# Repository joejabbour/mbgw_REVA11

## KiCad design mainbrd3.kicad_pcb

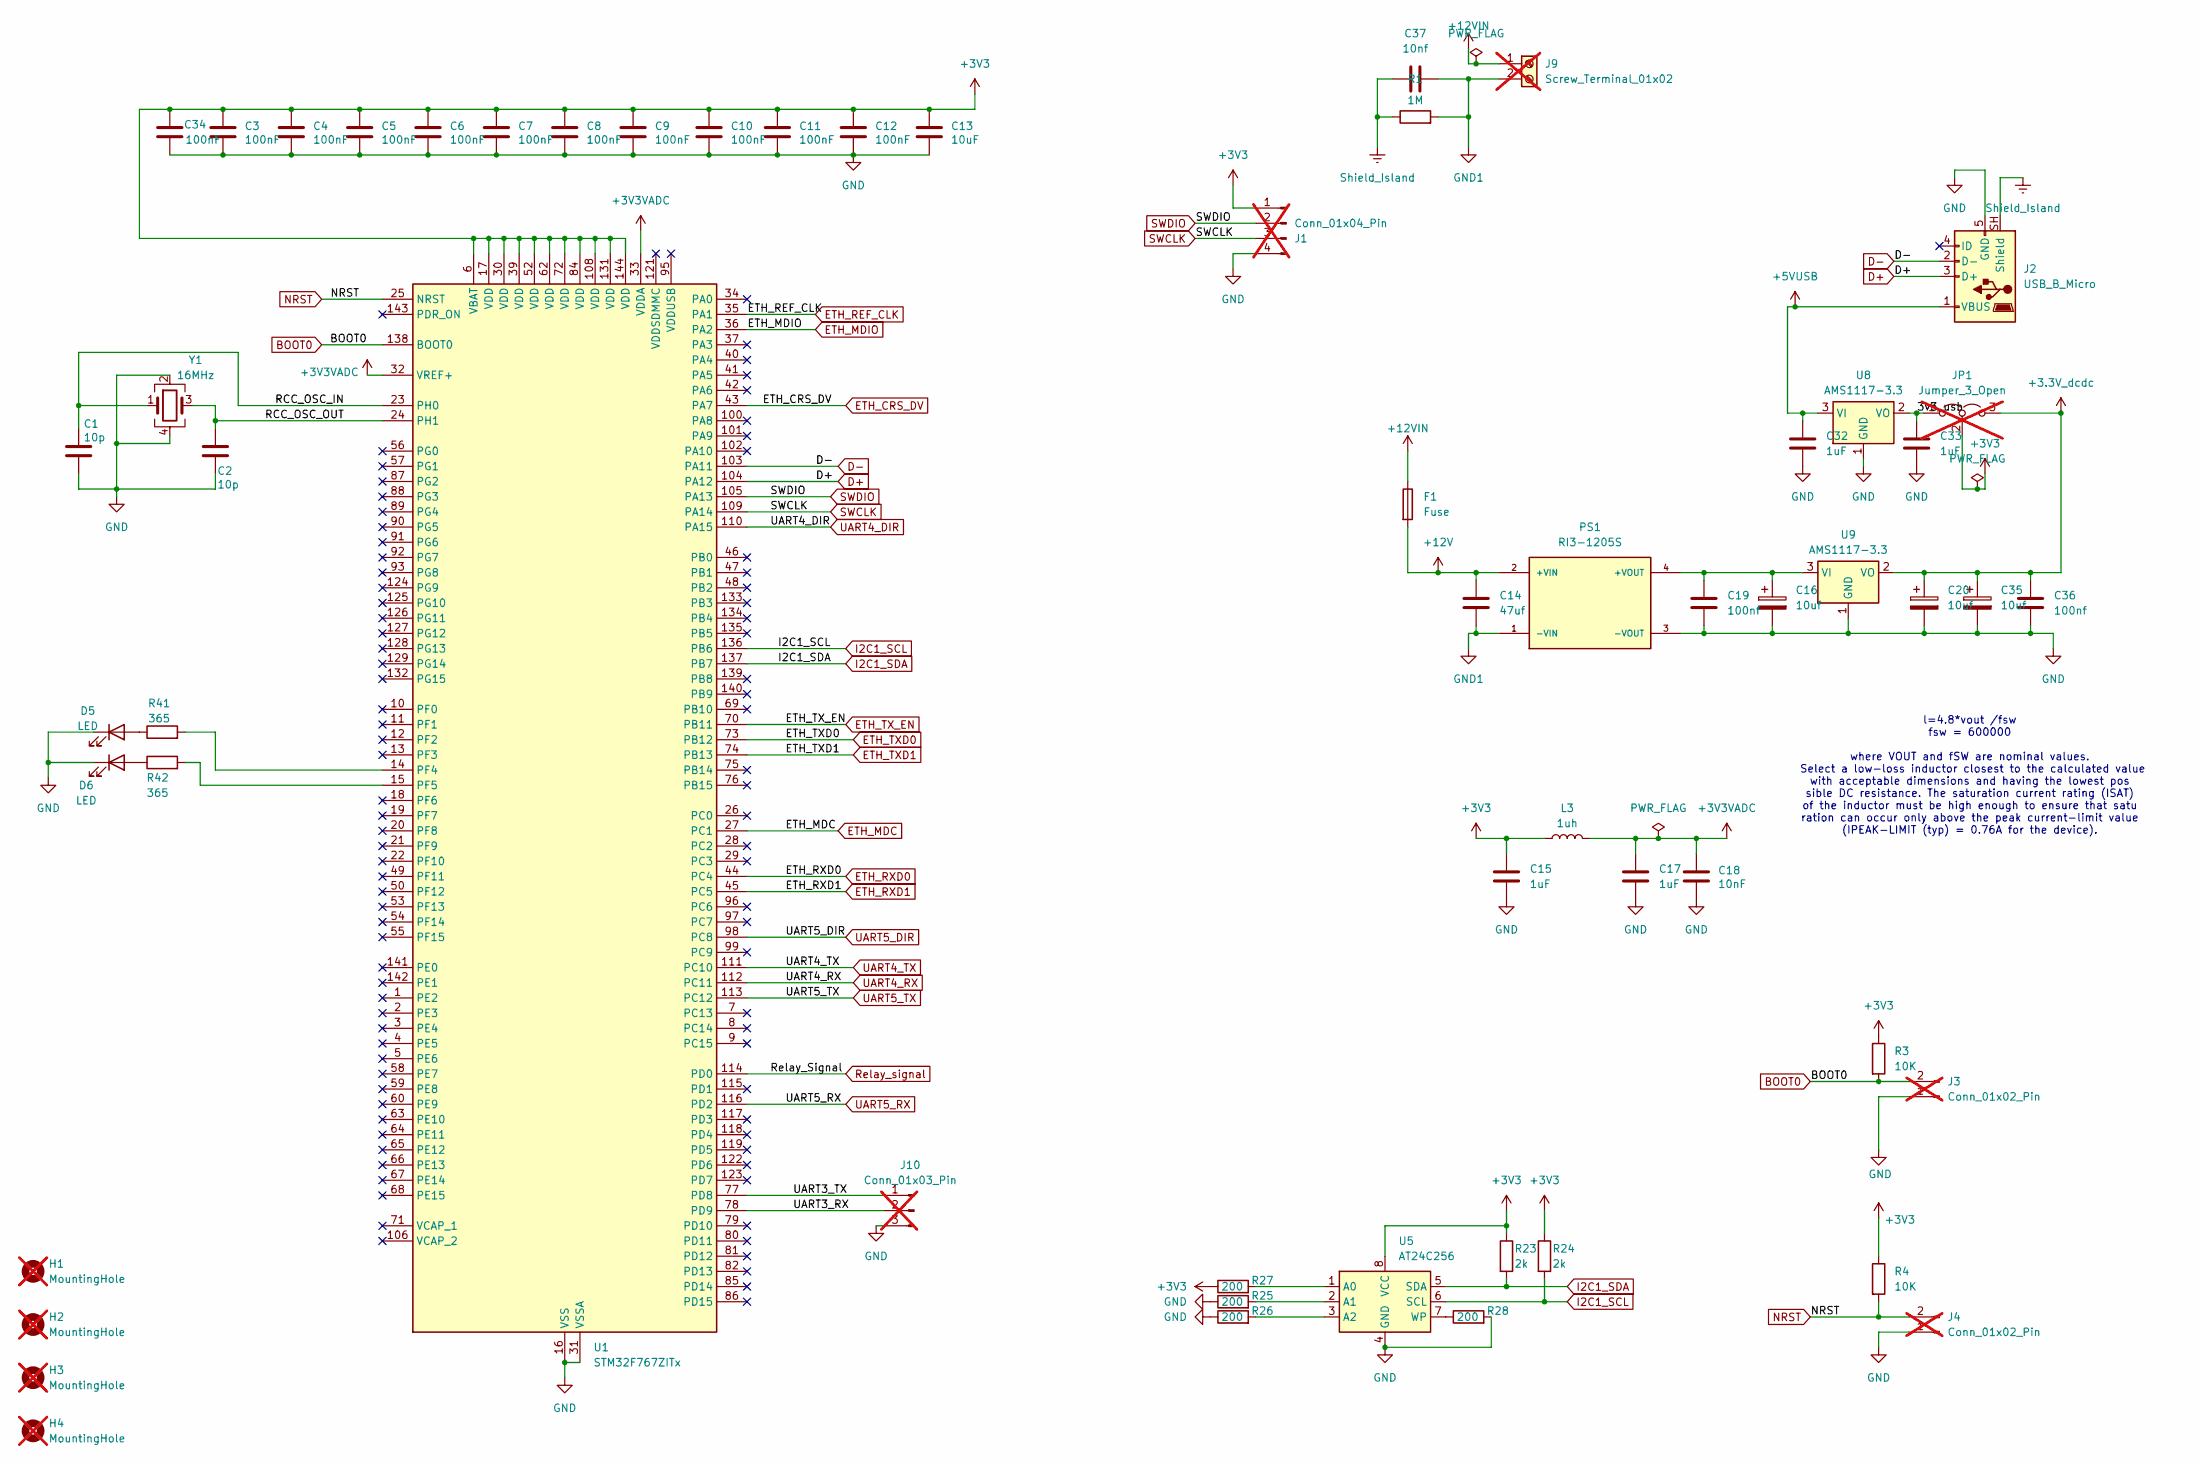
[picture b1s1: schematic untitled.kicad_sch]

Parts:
C1, C2: 10p; C_0402_1005Metric; MPN 0402CG100J500NT; JLCPCB PN C1545
C3, C4, C5, C6, C7, C8, C9, C10, C11, C12, C34: 100nF; C_0402_1005Metric; MPN 0402F104M500NT; JLCPCB PN C1581
C13: 10uF; C_0603_1608Metric; MPN CL10A106MQ8NNNC; JLCPCB PN C1691
C14: 47uf; C_1210_3225Metric; MPN GRM32ER61C476KE15L; LCSC C77101
C15, C17, C32, C33: 1uF; C_0402_1005Metric; MPN CL05A105KP5NNNC; JLCPCB PN C14445
C16, C20, C35: 10uf; CP_EIA-3216-18_Kemet-A; MPN TAJA106K016RNJ; LCSC C7171
C18: 10nF; C_0402_1005Metric; MPN 0402B103K500NT; JLCPCB PN C1524
C19, C36: 100nf; C_0402_1005Metric; MPN CC0402KRX7R7BB104; LCSC C60474
C37: 10nf; C_1812_4532Metric; MPN 1812B103K202NT; LCSC C574051
D5, D6: LED; LED_0603_1608Metric; MPN KT-0603R; JLCPCB PN C2286
F1: Fuse; Fuse_0603_1608Metric_Pad1.05x0.95mm_HandSolder; MPN 0467001.NRHF; LCSC C151139
H1, H2, H3, H4: MountingHole; MountingHole_2.2mm_M2; not fitted
J1: Conn_01x04_Pin; PinHeader_1x04_P2.54mm_Vertical; not fitted
J2: USB_B_Micro; USB_Micro-B_Wuerth_629105150521; JLCPCB PN 732-5960-2-ND(digi)
J3, J4: Conn_01x02_Pin; PinHeader_1x02_P2.54mm_Vertical; not fitted
J9: Screw_Terminal_01x02; TerminalBlock_Phoenix_MKDS-1,5-2-5.08_1x02_P5.08mm_Horizont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; not fitted
J10: Conn_01x03_Pin; PinHeader_1x03_P2.54mm_Vertical; not fitted
JP1: Jumper_3_Open; SolderJumper-3_P1.3mm_Open_Pad1.0x1.5mm; not fitted
L3: 1uh; L_0805_2012Metric; MPN MCL2012S1R0MT; JLCPCB PN C98325
PS1: RI3-1205S; CONV_RI3-1205S; PARTREV 3
R1: 1M; R_1206_3216Metric; MPN FRC1206J105 TS; LCSC C2907441
R3, R4: 10K; R_0402_1005Metric; MPN 0402WGJ0103TCE; JLCPCB PN C25531
R23, R24: 2k; R_0402_1005Metric; MPN 0402WGF2001TCE; JLCPCB PN C4109
R25, R26, R27, R28: 200; R_0402_1005Metric; MPN 0402WGF2000TCE; JLCPCB PN C25087
R41, R42: 365; R_0402_1005Metric; MPN 0402WGJ0361TCE; JLCPCB PN C25162
U1: STM32F767ZITx; LQFP-144_20x20mm_P0.5mm; MPN STM32F767ZIT6; JLCPCB PN C90235
U5: AT24C256; SOIC-8_3.9x4.9mm_P1.27mm; MPN AT24C256C-SSHL-T; JLCPCB PN C6482
U8, U9: AMS1117-3.3; SOT-223-3_TabPin2; MPN AMS1117-3.3; JLCPCB PN C6186
Y1: 16MHz; Crystal_SMD_3225-4Pin_3.2x2.5mm; MPN WTL3M01610; JLCPCB PN C2857621

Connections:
+3.3V_dcdc: C20.1, C35.1, C36.1, JP1.3 (B), U9.2 (VO)
+3V3: C3.1, C4.1, C5.1, C6.1, C7.1, C8.1, C9.1, C10.1, C11.1, C12.1, C13.1, C15.1, C34.1, J1.1, JP1.2 (C), L3.1, R3.1, R4.1, R23.1, R24.1, R27.1, U1.6 (VBAT), U1.17 (VDD), U1.30 (VDD), U1.39 (VDD), U1.52 (VDD), U1.62 (VDD), U1.72 (VDD), U1.84 (VDD), U1.108 (VDD), U1.131 (VDD), U1.144 (VDD), U5.8 (VCC); also elsewhere on the board
+3V3VADC: C17.1, C18.1, L3.2, U1.32 (VREF+), U1.33 (VDDA)
+5VUSB: C32.1, J2.1 (VBUS), U8.3 (VI)
+12V: C14.1, F1.2, PS1.2 (+VIN); also elsewhere on the board
+12VIN: F1.1, J9.1
/MCU/3v3_usb: C33.1, JP1.1 (A), U8.2 (VO)
/MCU/RCC_OSC_IN: C1.1, U1.23 (PH0), Y1.1
/MCU/RCC_OSC_OUT: C2.1, U1.24 (PH1), Y1.3
/MCU/UART3_RX: J10.2, U1.78 (PD9)
/MCU/UART3_TX: J10.1, U1.77 (PD8)
BOOT0: J3.2, R3.2, U1.138 (BOOT0)
D+: J2.3 (D+), U1.104 (PA12)
D-: J2.2 (D-), U1.103 (PA11)
ETH_CRS_DV: U1.43 (PA7); also elsewhere on the board
ETH_MDC: U1.27 (PC1); also elsewhere on the board
ETH_MDIO: U1.36 (PA2); also elsewhere on the board
ETH_REF_CLK: U1.35 (PA1); also elsewhere on the board
ETH_RXD0: U1.44 (PC4); also elsewhere on the board
ETH_RXD1: U1.45 (PC5); also elsewhere on the board
ETH_TXD0: U1.73 (PB12); also elsewhere on the board
ETH_TXD1: U1.74 (PB13); also elsewhere on the board
ETH_TX_EN: U1.70 (PB11); also elsewhere on the board
GND: C1.2, C2.2, C3.2, C4.2, C5.2, C6.2, C7.2, C8.2, C9.2, C10.2, C11.2, C12.2, C13.2, C15.2, C16.2, C17.2, C18.2, C19.2, C20.2, C32.2, C33.2, C34.2, C35.2, C36.2, D5.1 (K), D6.1 (K), J1.4, J2.5 (GND), J3.1, J4.1, J10.3, PS1.3 (-VOUT), R25.1, R26.1, R28.2, U1.16 (VSS), U1.31 (VSSA), U1.38 (VSS), U1.51 (VSS), U1.61 (VSS), U1.83 (VSS), U1.94 (VSS), U1.107 (VSS), U1.120 (VSS), U1.130 (VSS), U5.4 (GND), U8.1 (GND), U9.1 (GND), Y1.2, Y1.4; also elsewhere on the board
GND1: C14.2, C37.2, J9.2, PS1.1 (-VIN), R1.2; also elsewhere on the board
I2C1_SCL: R24.2, U1.136 (PB6), U5.6 (SCL)
I2C1_SDA: R23.2, U1.137 (PB7), U5.5 (SDA)
NRST: J4.2, R4.2, U1.25 (NRST); also elsewhere on the board
unnamed: D5.2 (A), R41.1
unnamed: D6.2 (A), R42.1
unnamed: C16.1, C19.1, PS1.4 (+VOUT), U9.3 (VI)
unnamed: R41.2, U1.14 (PF4)
unnamed: R42.2, U1.15 (PF5)
unnamed: R27.2, U5.1 (A0)
unnamed: R25.2, U5.2 (A1)
unnamed: R26.2, U5.3 (A2)
unnamed: R28.1, U5.7 (WP)
Relay_signal: U1.114 (PD0); also elsewhere on the board
SWCLK: J1.3, U1.109 (PA14)
SWDIO: J1.2, U1.105 (PA13)
Shield_Island: C37.1, J2.SH (Shield), R1.1; also elsewhere on the board
UART4_DIR: U1.110 (PA15); also elsewhere on the board
UART4_RX: U1.112 (PC11); also elsewhere on the board
UART4_TX: U1.111 (PC10); also elsewhere on the board
UART5_DIR: U1.98 (PC8); also elsewhere on the board
UART5_RX: U1.116 (PD2); also elsewhere on the board
UART5_TX: U1.113 (PC12); also elsewhere on the board

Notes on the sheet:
l=4.8*vout /fsw fsw = 600000 where VOUT and fSW are nominal values. Select a low-loss inductor closest to the calculated value with acceptable dimensions and having the lowest pos sible DC resistance. The saturation current rating (ISAT) of the inductor must be high enough to ensure that satu ratio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

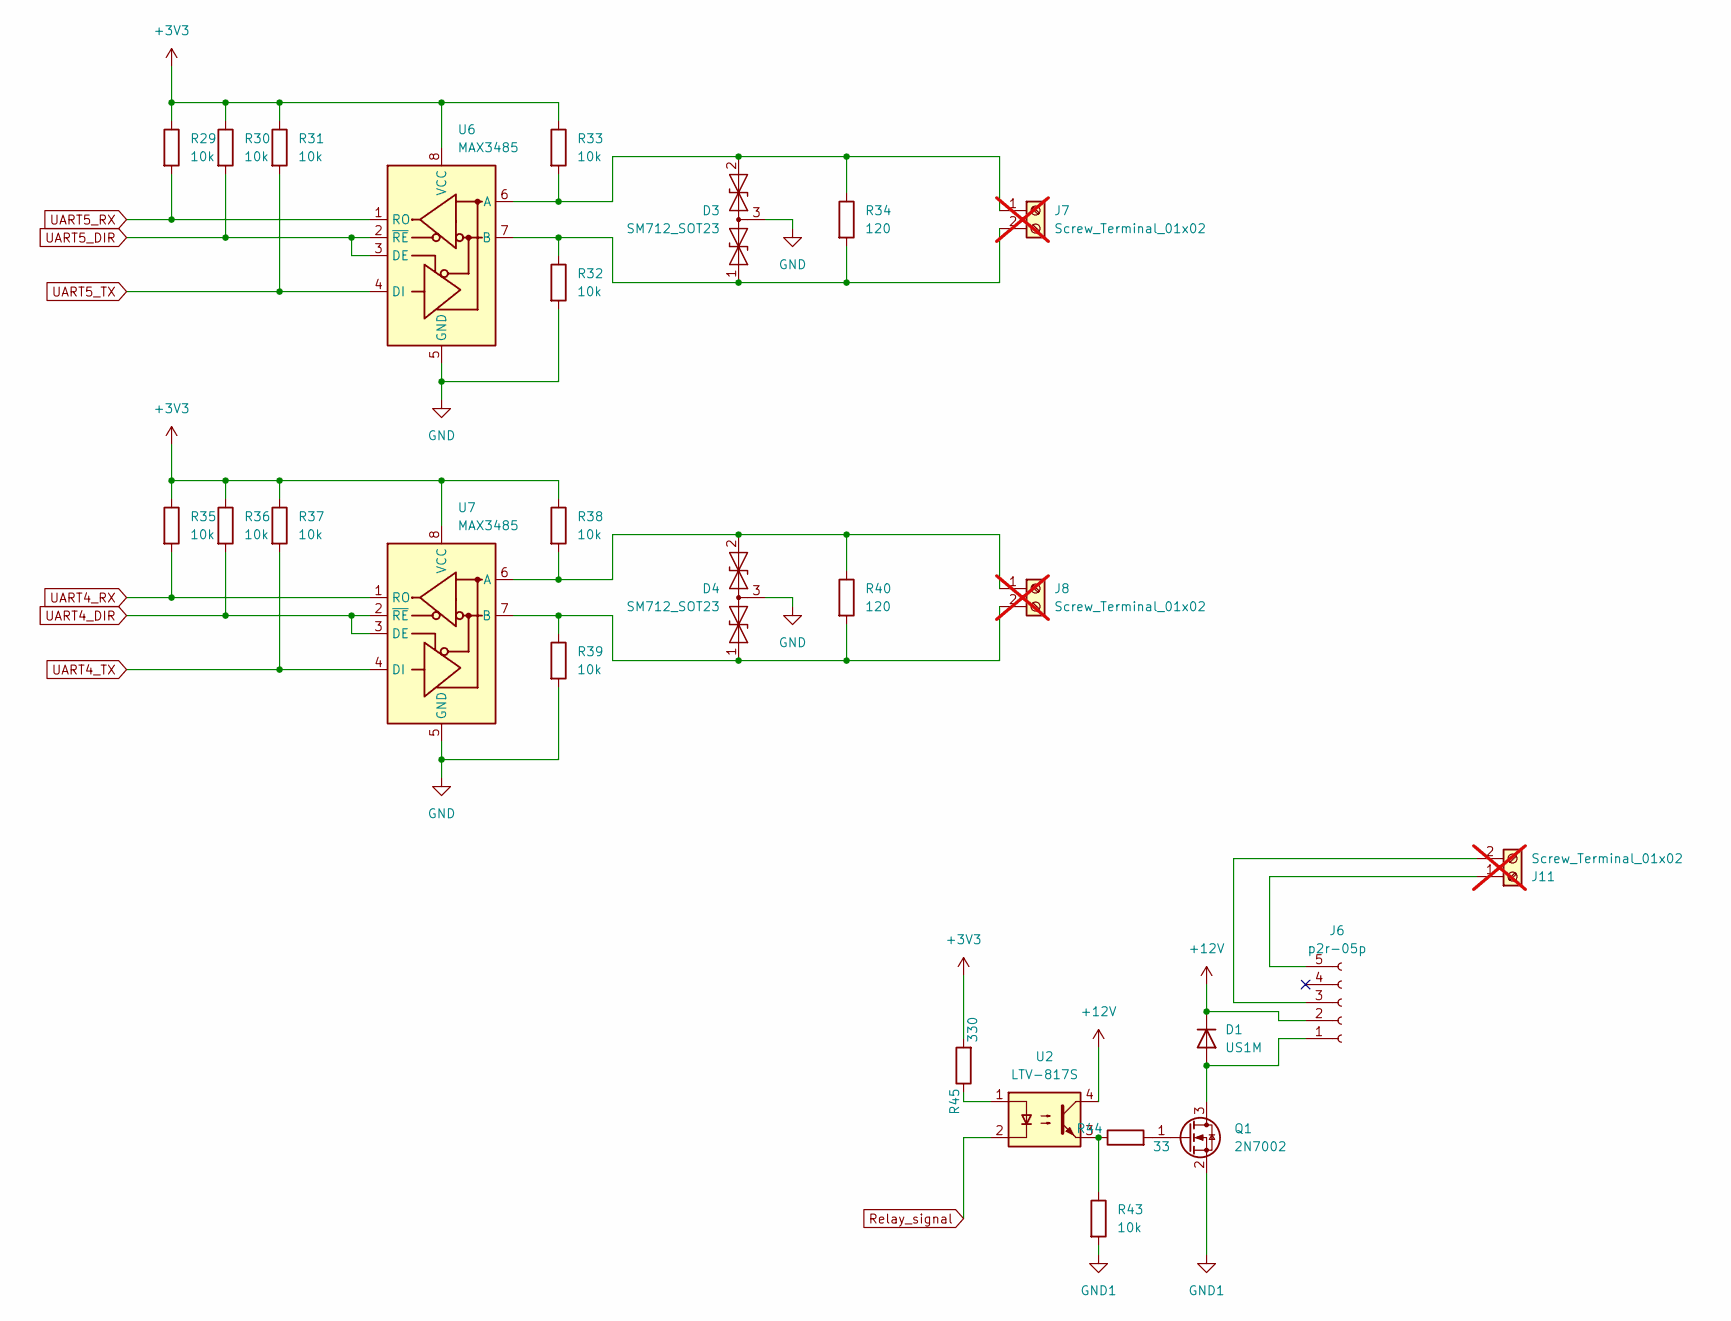
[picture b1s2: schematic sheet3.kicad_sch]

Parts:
D1: US1M; D_SMA
D3, D4: SM712_SOT23; SOT-23; MPN SM712; JLCPCB PN C293966
J6: p2r-05p; P2R-05P
J7, J8, J11: Screw_Terminal_01x02; TerminalBlock_Phoenix_MKDS-1,5-2-5.08_1x02_P5.08mm_Horizont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; not fitted
Q1: 2N7002; SOT-23; MPN 2N7002; LCSC C916396
R29, R30, R31, R32, R33, R35, R36, R37, R38, R39, R43: 10k; R_0402_1005Metric; MPN 0402WGJ0103TCE; JLCPCB PN C25531
R34, R40: 120; R_0402_1005Metric; MPN 0402WGF1200TCE; JLCPCB PN C25079
R44: 33; R_0402_1005Metric; MPN 0402WGF330JTCE; JLCPCB PN C25105
R45: 330; C_0603_1608Metric; MPN RC0603FR-07330RL; JLCPCB PN C105881
U2: LTV-817S; SMDIP-4_W9.53mm; MPN LTV-817S-TA1-B; LCSC C109227
U6, U7: MAX3485; SOIC-8_3.9x4.9mm_P1.27mm; MPN MAX3485ESA(UMW); JLCPCB PN C668204

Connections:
+3V3: R29.1, R30.1, R31.1, R33.1, R35.1, R36.1, R37.1, R38.1, R45.2, U6.8 (VCC), U7.8 (VCC); also elsewhere on the board
+12V: D1.1 (K), J6.2 (coil_pos), U2.4; also elsewhere on the board
GND: D3.3 (common), D4.3 (common), R32.2, R39.2, U6.5 (GND), U7.5 (GND); also elsewhere on the board
GND1: Q1.2 (S), R43.2; also elsewhere on the board
unnamed: D1.2 (A), J6.1 (coil_neg), Q1.3 (D)
unnamed: D3.1 (A1), J7.2, R32.1, R34.2, U6.7 (B)
unnamed: D3.2 (A2), J7.1, R33.2, R34.1, U6.6 (A)
unnamed: D4.1 (A1), J8.2, R39.1, R40.2, U7.7 (B)
unnamed: D4.2 (A2), J8.1, R38.2, R40.1, U7.6 (A)
unnamed: J6.5 (NO), J11.1
unnamed: J6.3 (Common), J11.2
unnamed: Q1.1 (G), R44.2
unnamed: R43.1, R44.1, U2.3
unnamed: R45.1, U2.1
Relay_signal: U2.2; also elsewhere on the board
UART4_DIR: R36.2, U7.2 (~RE), U7.3 (DE); also elsewhere on the board
UART4_RX: R35.2, U7.1 (RO); also elsewhere on the board
UART4_TX: R37.2, U7.4 (DI); also elsewhere on the board
UART5_DIR: R30.2, U6.2 (~RE), U6.3 (DE); also elsewhere on the board
UART5_RX: R29.2, U6.1 (RO); also elsewhere on the board
UART5_TX: R31.2, U6.4 (DI); also elsewhere on the board

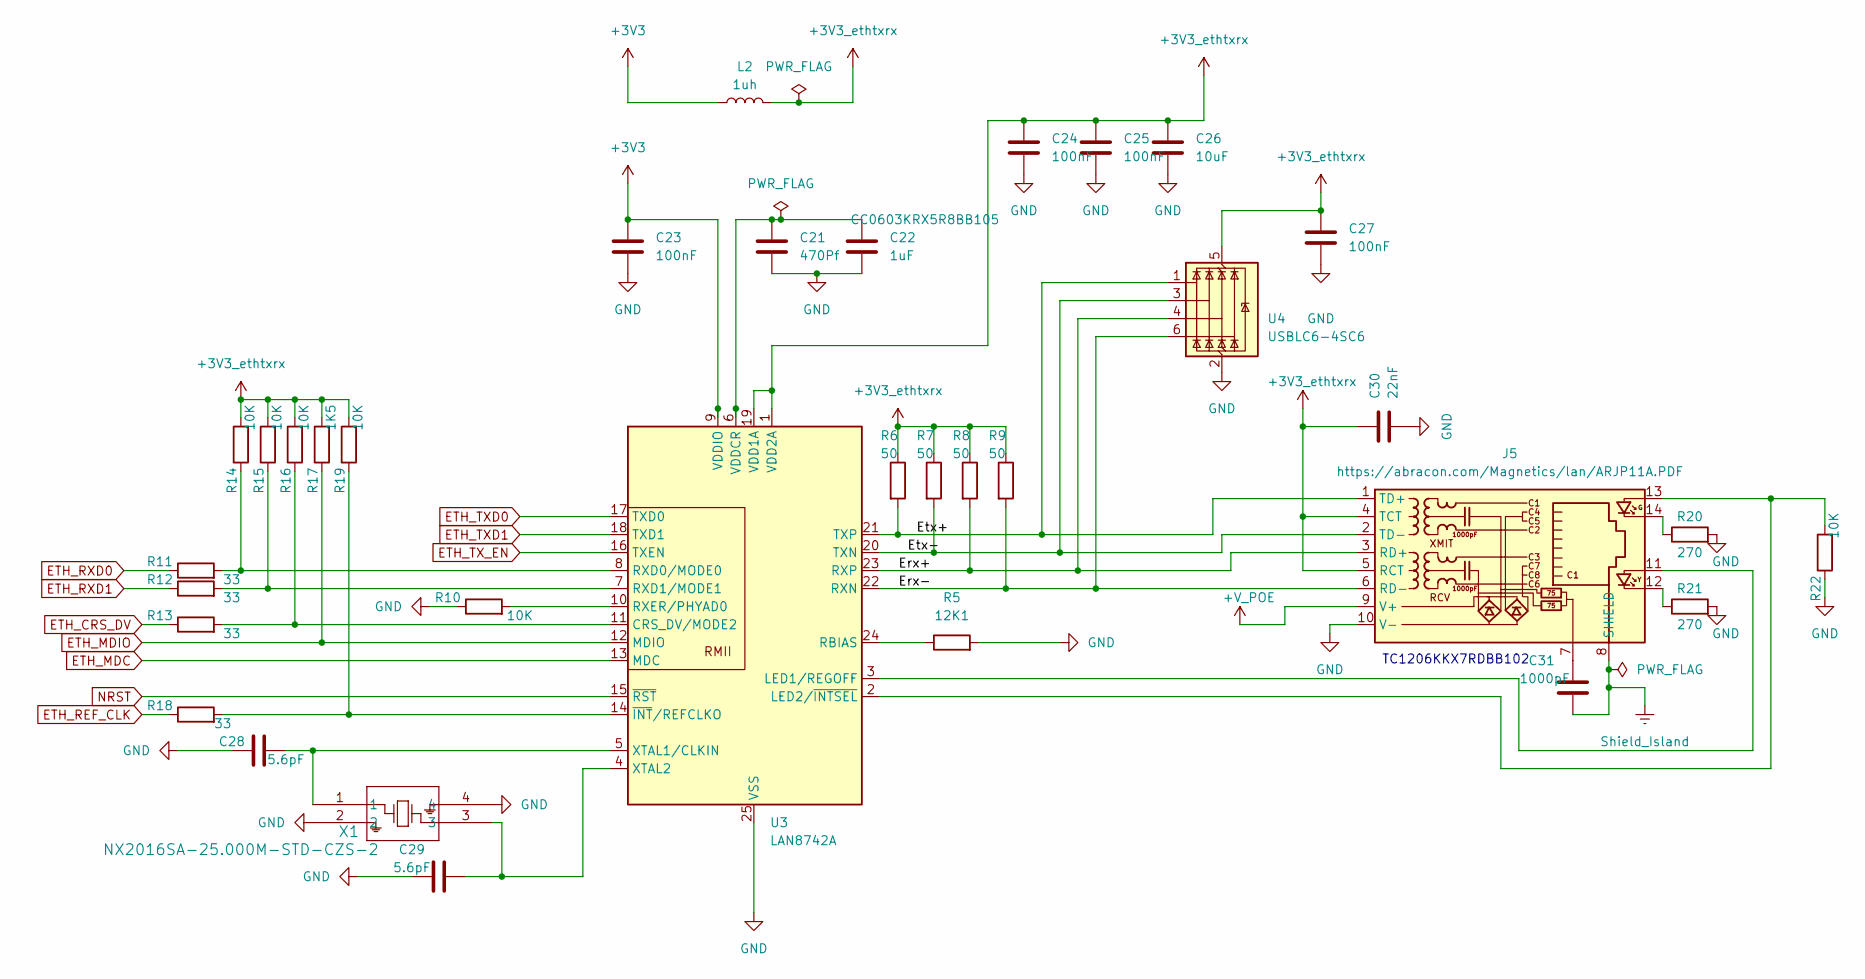
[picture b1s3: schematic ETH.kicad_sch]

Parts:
C21: 470Pf; C_0402_1005Metric; MPN 0402B471K500NT; JLCPCB PN C1537
C22: 1uF; C_0603_1608Metric; MPN CC0603KRX5R8BB105; JLCPCB PN C14664
C23, C24, C25, C27: 100nF; C_0402_1005Metric; MPN 0402F104M500NT; JLCPCB PN C1581
C26: 10uF; C_0402_1005Metric; MPN CL05A106MQ5NUNC; JLCPCB PN C15525
C28, C29: 5.6pF; C_0402_1005Metric; MPN 0402CG5R6C500NT; JLCPCB PN C1574
C30: 22nF; C_0402_1005Metric; MPN 0402B223K500NT; JLCPCB PN C1532
C31: 1000pF; C_1206_3216Metric; MPN CC1206KKX7RDBB102; JLCPCB PN C23631
J5: https://abracon.com/Magnetics/lan/ARJP11A.PDF; RJ45_Abracon_ARJP11A-MA_Horizontal; JLCPCB PN ARJP11A-MASA-B-A-EMU2-ND(digi)
L2: 1uh; L_0805_2012Metric; MPN MCL2012S1R0MT; JLCPCB PN C98325
R5: 12K1; R_0402_1005Metric; MPN 0402WGF1212TCE; JLCPCB PN C25852
R6, R7, R8, R9: 50; R_0402_1005Metric; MPN AC0402JR-0750RL; JLCPCB PN C227387
R10, R14, R15, R16, R19, R22: 10K; R_0402_1005Metric; MPN 0402WGJ0103TCE; JLCPCB PN C25531
R11, R12, R13, R18: 33; R_0402_1005Metric; MPN 0402WGF330JTCE; JLCPCB PN C25105
R17: 1K5; R_0402_1005Metric; MPN 0402WGF1501TCE; JLCPCB PN C25867
R20, R21: 270; R_0402_1005Metric; MPN RTT022700FTH; JLCPCB PN C11429
U3: LAN8742A; VQFN-24-1EP_4x4mm_P0.5mm_EP2.5x2.5mm_ThermalVias; MPN LAN8742AI-CZ-TR; JLCPCB PN C621425
U4: USBLC6-4SC6; SOT-23-6; JLCPCB PN 497-4492-2-ND(digi)
X1: NX2016SA-25.000M-STD-CZS-2; NX2016SA_NDK; MPN NX2016SA-25MHZ-STD-CZS-2; JLCPCB PN C843258

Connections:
+3V3: C23.1, L2.1, U3.9 (VDDIO); also elsewhere on the board
+3V3_ethtxrx: C24.1, C25.1, C26.1, C27.1, C30.1, J5.4 (TCT), J5.5 (RCT), L2.2, R6.1, R7.1, R8.1, R9.1, R14.2, R15.2, R16.2, R17.2, R19.2, U3.1 (VDD2A), U3.19 (VDD1A), U4.5 (VBUS)
+V_POE: J5.9 (V+)
/ETH/Erx+: J5.3 (RD+), R8.2, U3.23 (RXP), U4.4 (I/O3)
/ETH/Erx-: J5.6 (RD-), R9.2, U3.22 (RXN), U4.6 (I/O4)
/ETH/Etx+: J5.1 (TD+), R6.2, U3.21 (TXP), U4.1 (I/O1)
/ETH/Etx-: J5.2 (TD-), R7.2, U3.20 (TXN), U4.3 (I/O2)
ETH_CRS_DV: R13.1; also elsewhere on the board
ETH_MDC: U3.13 (MDC); also elsewhere on the board
ETH_MDIO: R17.1, U3.12 (MDIO); also elsewhere on the board
ETH_REF_CLK: R18.1; also elsewhere on the board
ETH_RXD0: R11.1; also elsewhere on the board
ETH_RXD1: R12.1; also elsewhere on the board
ETH_TXD0: U3.17 (TXD0); also elsewhere on the board
ETH_TXD1: U3.18 (TXD1); also elsewhere on the board
ETH_TX_EN: U3.16 (TXEN); also elsewhere on the board
GND: C21.2, C22.2, C23.2, C24.2, C25.2, C26.2, C27.2, C28.2, C29.1, C30.2, J5.10 (V-), R5.2, R10.1, R20.2, R21.2, R22.1, U3.25 (VSS), U4.2 (GND), X1.2, X1.4; also elsewhere on the board
NRST: U3.15 (~RST); also elsewhere on the board
unnamed: C31.1, J5.7
unnamed: J5.12, R21.1
unnamed: J5.14, R20.1
unnamed: R13.2, R16.1, U3.11 (CRS_DV/MODE2)
unnamed: J5.11, U3.3 (LED1/REGOFF)
unnamed: J5.13, R22.2, U3.2 (LED2/~INTSEL)
unnamed: R5.1, U3.24 (RBIAS)
unnamed: R11.2, R14.1, U3.8 (RXD0/MODE0)
unnamed: R12.2, R15.1, U3.7 (RXD1/MODE1)
unnamed: R10.2, U3.10 (RXER/PHYAD0)
unnamed: C21.1, C22.1, U3.6 (VDDCR)
unnamed: C28.1, U3.5 (XTAL1/CLKIN), X1.1
unnamed: C29.2, U3.4 (XTAL2), X1.3
unnamed: R18.2, R19.1, U3.14 (~INT/REFCLKO)
Shield_Island: C31.2, J5.8 (SHIELD); also elsewhere on the board

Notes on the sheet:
TC1206KKX7RDBB102

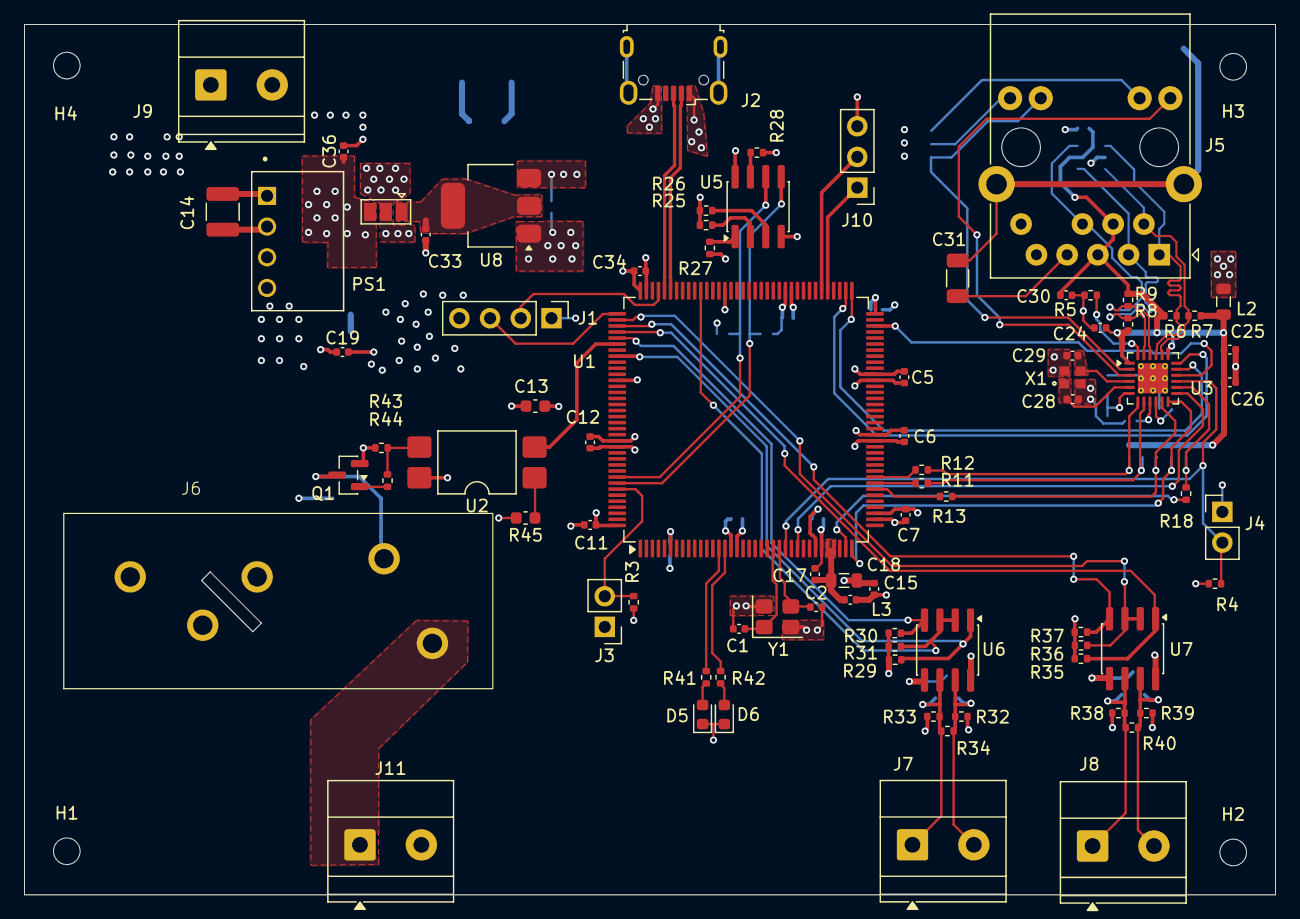
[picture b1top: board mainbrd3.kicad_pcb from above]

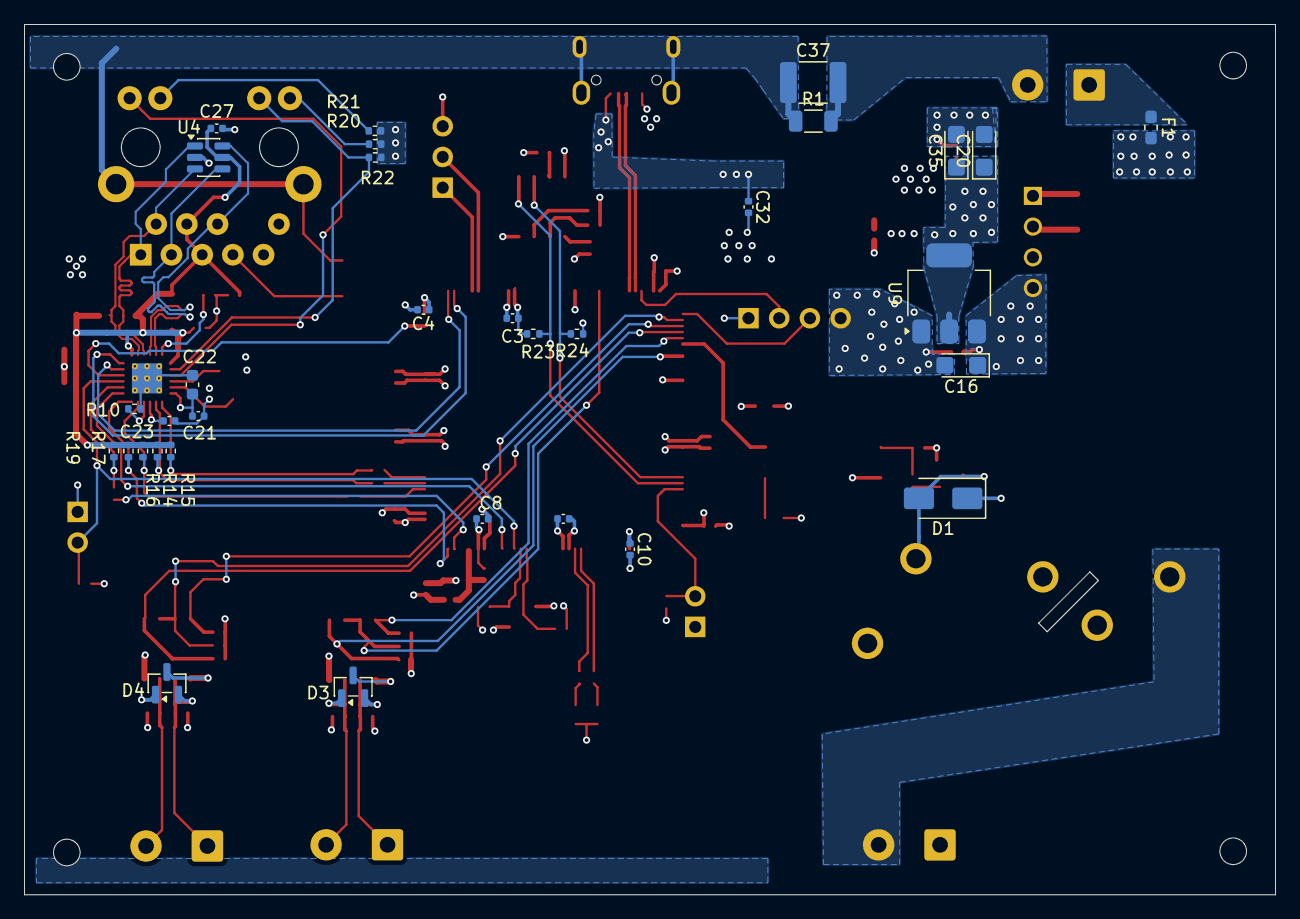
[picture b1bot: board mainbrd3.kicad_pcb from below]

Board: 4 copper layers, 103.5 x 72.0 mm, 118 parts (32 on the bottom side), 76 nets.

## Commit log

2026-04-18 Initial snapshot: 3 files changed mainbrd3.kicad_pcb 2/0/0 mainbrd3.kicad_pro 1/0/0 mainbrd3.kicad_sch 14/0/0
2026-04-18 Autosave
2026-04-18 PCB Save: 5 files changed mainbrd3.kicad_pcb 25636/0/2 mainbrd3.kicad_prl 129/0/0 mainbrd3.kicad_pro 693/0/1 ~mainbrd3.kicad_pcb.lck 1/0/0 ~mainbrd3.kicad_sch.lck 1/0/0
2026-04-18 PCB Save: 2 files changed mainbrd3.kicad_pcb 0/0/469 mainbrd3.kicad_prl 0/0/1
2026-04-18 SCH Save: 1 files changed untitled.kicad_sch 0/10/205
2026-04-18 SCH Save: 1 files changed sheet3.kicad_sch 0/0/24
2026-04-18 SCH Save: 2 files changed mainbrd3.kicad_pro 6/0/1 mainbrd3.kicad_sch 25/0/9
2026-04-18 SCH Save: 1 files changed ETH.kicad_sch 0/0/68
2026-04-23 PCB Save: 2 files changed mainbrd3.kicad_pcb 40/0/0 mainbrd3.kicad_pro 17/0/1
2026-04-23 PCB Save: 3 files changed mainbrd3.kicad_pcb 861/0/135 mainbrd3.kicad_prl 13/0/4 ~mainbrd3.kicad_pro.lck 1/0/0
2026-04-23 PCB Save: 2 files changed mainbrd3.kicad_pcb 1188/0/386 mainbrd3.kicad_prl 0/0/2
2026-04-23 PCB Save: 1 files changed mainbrd3.kicad_prl 0/0/2
2026-04-25 PCB Save: 3 files changed mainbrd3.kicad_pcb 748/0/2692 mainbrd3.kicad_prl 0/0/2 mainbrd3.kicad_pro 0/0/1
2026-04-25 PCB Save: 2 files changed mainbrd3.kicad_pcb 79/0/261 mainbrd3.kicad_prl 0/0/2
2026-04-25 PCB Save: 3 files changed mainbrd3.kicad_pcb 0/38/838 mainbrd3.kicad_prl 0/0/2 mainbrd3.kicad_pro 0/0/1
2026-04-26 PCB Save: 3 files changed mainbrd3.kicad_pcb 627/0/725 mainbrd3.kicad_prl 0/0/1 mainbrd3.kicad_pro 0/0/1
2026-04-26 PCB Save: 2 files changed mainbrd3.kicad_pcb 12/0/1718 mainbrd3.kicad_prl 0/0/1
2026-04-26 PCB Save: 1 files changed mainbrd3.kicad_pcb 437/0/814
2026-04-26 PCB Save: 3 files changed mainbrd3.kicad_pcb 3388/0/1892 mainbrd3.kicad_prl 0/0/2 mainbrd3.kicad_pro 0/0/3
2026-05-03 PCB Save: 1 files changed mainbrd3.kicad_pcb 1419/0/1758
2026-05-03 PCB Save: 1 files changed mainbrd3.kicad_pcb 500/0/531
2026-05-03 PCB Save: 2 files changed mainbrd3.kicad_pcb 351/0/833 mainbrd3.kicad_prl 0/0/1
2026-05-04 PCB Save: 2 files changed mainbrd3.kicad_pcb 2103/0/7861 mainbrd3.kicad_prl 0/0/2
2026-05-04 PCB Save: 3 files changed mainbrd3.kicad_prl 0/0/1 REVA1-1.kicad_pcb 37353/0/0 REVA1-1.kicad_pro 717/0/0
2026-05-05 PCB Save: 2 files changed mainbrd3.kicad_pcb 0/1115/2443 mainbrd3.kicad_prl 0/0/1
2026-05-05 PCB Save: 1 files changed mainbrd3.kicad_prl 0/0/1
2026-05-05 PCB Save: 2 files changed mainbrd3.kicad_pcb 55/0/0 mainbrd3.kicad_prl 0/0/1
2026-05-05 PCB Save: 1 files changed mainbrd3.kicad_pcb 0/1609/14497
2026-05-05 PCB Save: 1 files changed mainbrd3.kicad_pcb 884/0/1505
2026-05-05 PCB Save: 1 files changed mainbrd3.kicad_pcb 0/8/243
2026-05-06 SCH Save: 1 files changed untitled.kicad_sch 0/617/2
2026-05-06 SCH Save: 1 files changed sheet3.kicad_sch 0/2/12
2026-05-06 PCB Save: 1 files changed mainbrd3.kicad_pcb 1980/0/2540
2026-05-06 PCB Save: 2 files changed mainbrd3.kicad_pcb 402/0/1099 mainbrd3.kicad_prl 0/0/1
2026-05-06 PCB Save: 1 files changed mainbrd3.kicad_pcb 95/0/467
2026-05-06 PCB Save: 1 files changed mainbrd3.kicad_pcb 257/0/873
2026-05-06 PCB Save: 2 files changed mainbrd3.kicad_pcb 679/0/2551 mainbrd3.kicad_prl 0/0/1
2026-05-06 PCB Save: 1 files changed mainbrd3.kicad_pcb 32/0/61
2026-05-06 PCB Save: 3 files changed mainbrd3.kicad_pcb 0/19/2243 mainbrd3.kicad_prl 0/0/1 mainbrd3.kicad_pro 0/0/1
2026-05-07 PCB Save: 2 files changed mainbrd3.kicad_pcb 273/0/2220 mainbrd3.kicad_prl 0/0/2
2026-05-07 PCB Save: 2 files changed mainbrd3.kicad_pcb 0/157/2515 mainbrd3.kicad_prl 0/0/1
2026-05-11 Pre-restore backup: 10 files changed mainbrd3.kicad_prl 143/0/0 mainbrd3.kicad_pro 735/0/0 REVA1-1.kicad_pcb 37353/0/0 REVA1-1.kicad_prl 143/0/0 REVA1-1.kicad_pro 717/0/0 REVA1-2.kicad_pcb 39102/0/0 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
2026-05-11 Restored from 6c1fd55b7c2569fc9f5223d0e45c5a76d0a9d4a9 2026-05-11T21:21:02
2026-05-11 Restored from 084cf424a3c1a4c76f6c3265bbeb2fc9830a544d 2026-05-11T21:32:41
2026-05-19 Pre-restore backup: 6 files changed fp-lib-table 4/0/0 ImportGuides.html 96/0/0 mainbrd3.kicad_prl 0/1/3 mainbrd3.kicad_pro 6/0/3 REVA11.kicad_pcb 39583/0/0 REVA11.kicad_pro 741/0/0
2026-05-19 Restored from 0e2a30bd2508e00d4570fdbcd08fa9bf24896dcd 2026-05-19T22:47:51
